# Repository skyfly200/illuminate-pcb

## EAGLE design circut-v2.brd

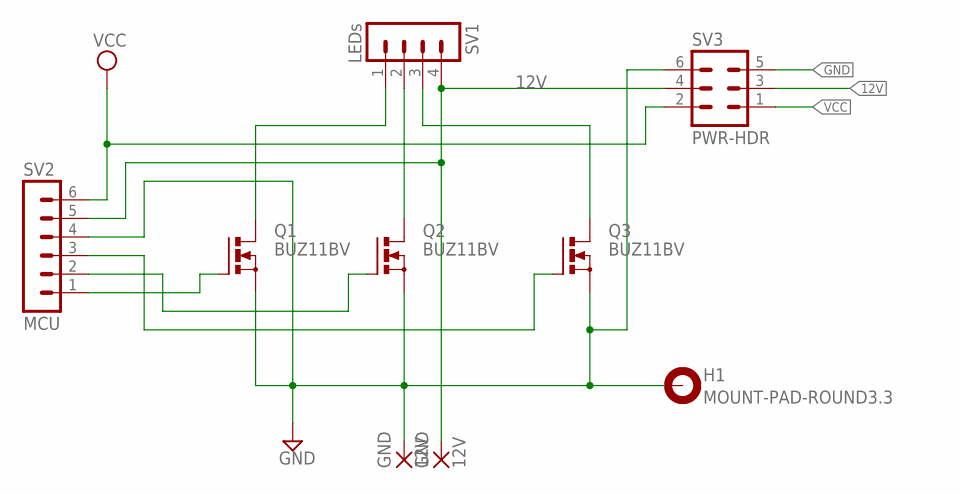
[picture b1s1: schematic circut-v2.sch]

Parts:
12V: 12V; 3,17/1,3
GND: GND; 3,17/1,3
H1: MOUNT-PAD-ROUND3.3; 3,3-PAD
Q1, Q2, Q3: BUZ11BV; TO220BV
SV1: LEDs; MA04-1
SV2: MCU; MA06-1
SV3: PWR-HDR; MA03-2

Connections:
12V: 12V.1, SV1.4, SV2.5, SV3.3, SV3.4
C1: Q1.G, SV2.1
C2: Q2.G, SV2.2
C3: Q3.G, SV2.3
GND: GND.1, H1.B3,3, Q1.S, Q2.S, Q3.S, SV2.4, SV3.5, SV3.6
L1: Q1.D, SV1.1
L2: Q2.D, SV1.2
L3: Q3.D, SV1.3
VCC: SV2.6, SV3.1, SV3.2

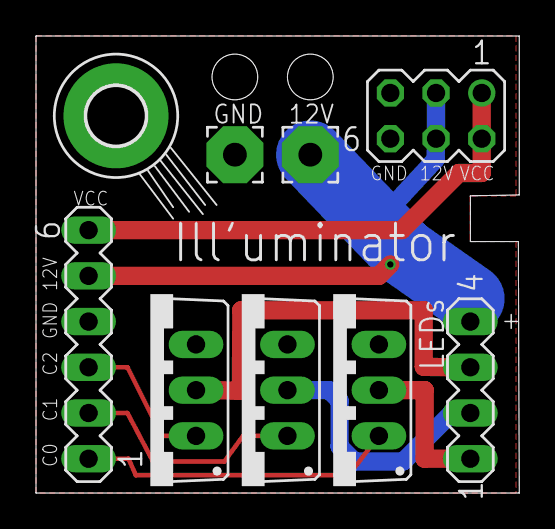
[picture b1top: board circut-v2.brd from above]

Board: 2 copper layers, 26.8 x 25.4 mm, 9 parts (0 on the bottom side), 9 nets.

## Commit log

2019-12-20 upload eagle files
